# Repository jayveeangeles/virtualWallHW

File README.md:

# virtualWallHW

## Project Brief:
Repository to hold EAGLE files for Roomba Virtual Wall using PIC12F683

## Notes:
1) R7 was replaced by a 0 ohm resistor. 
2) C6 was also removed from the circuit. 
3) [SeeedStudio script](http://support.seeedstudio.com/knowledgebase/articles/1176949-how-to-generate-gerber-file-from-eagle) was used to generate manufacturing files.
4) Only the panelized brd file is included in this package. The schematic of the other board will be posted once that has been verified.

## Firmware:
[Firmware link](https://github.com/jayveeangeles/virtualWallFW)

## References:
1) [High-Speed Layout Guidelines](http://www.ti.com/lit/an/scaa082a/scaa082a.pdf)
2) [Oscillator](http://ww1.microchip.com/downloads/en/DeviceDoc/31002a.pdf)
3) [EXTERNAL 32.768 KHZ CRYSTAL OSCILLATOR](https://www.silabs.com/documents/public/application-notes/AN299.pdf)
4) [Choosing the Right Crystal and Caps for your Design](https://blog.adafruit.com/2012/01/24/choosing-the-right-crystal-and-caps-for-your-design/)
5) [Summary of Eagle PCB Layout Guidelines](https://iotexpert.com/2016/11/16/eagle-pcb-layout-guidelines-osh-park/)
6) [Using EAGLE: Board Layout](https://learn.sparkfun.com/tutorials/using-eagle-board-layout)
7) [Adding copper pour in EAGLE](https://www.lucidar.me/en/eagle/adding-copper-pour-in-eagle/)
8) [EAGLE: Panelizing made easy](https://smdprutser.nl/blog/eagle-panelizing-made-easy/)

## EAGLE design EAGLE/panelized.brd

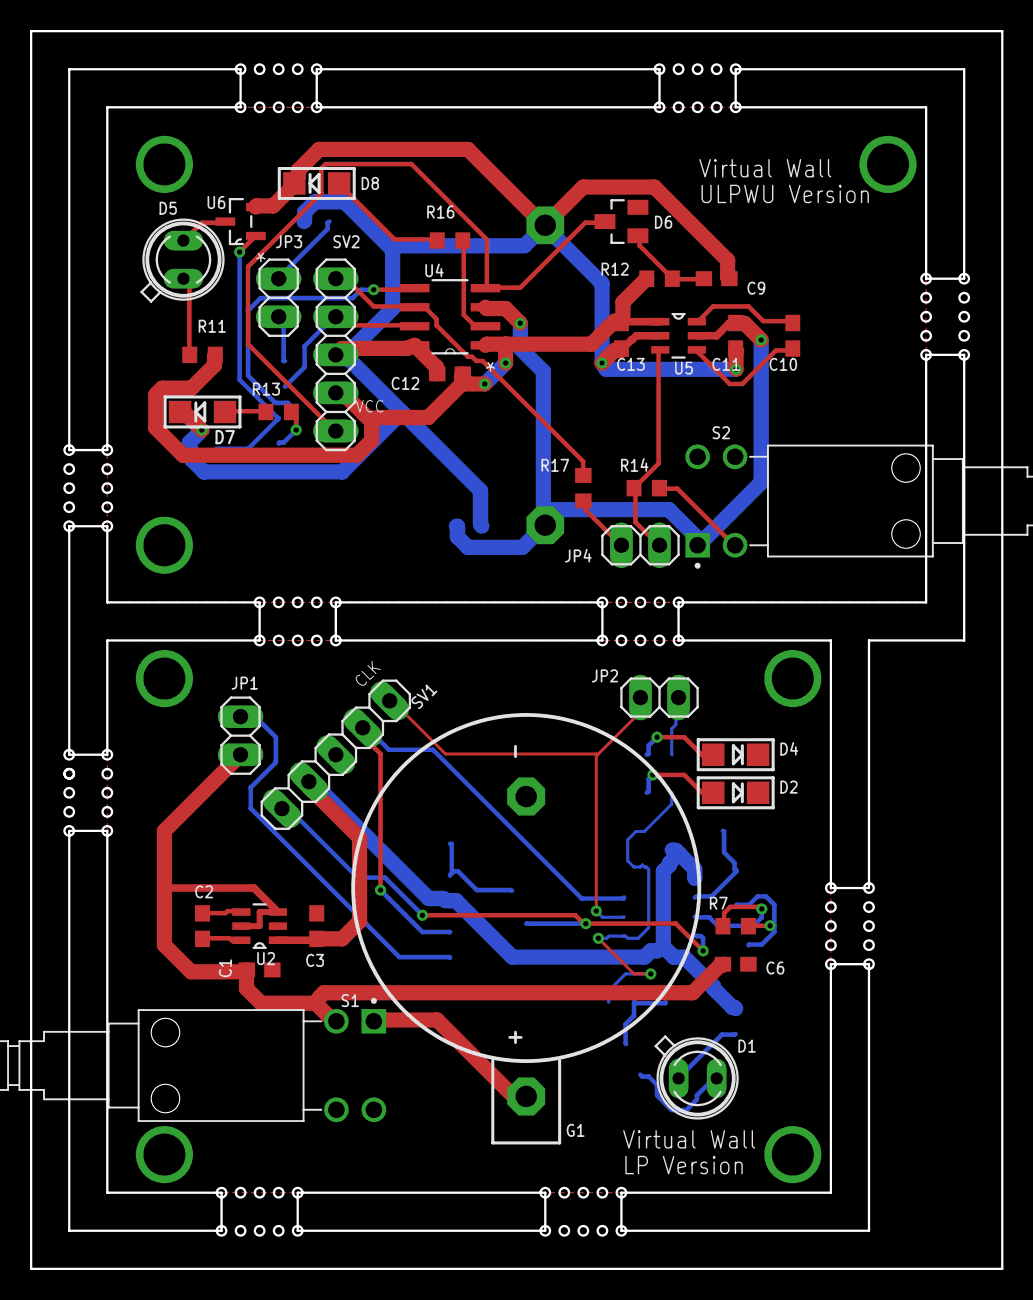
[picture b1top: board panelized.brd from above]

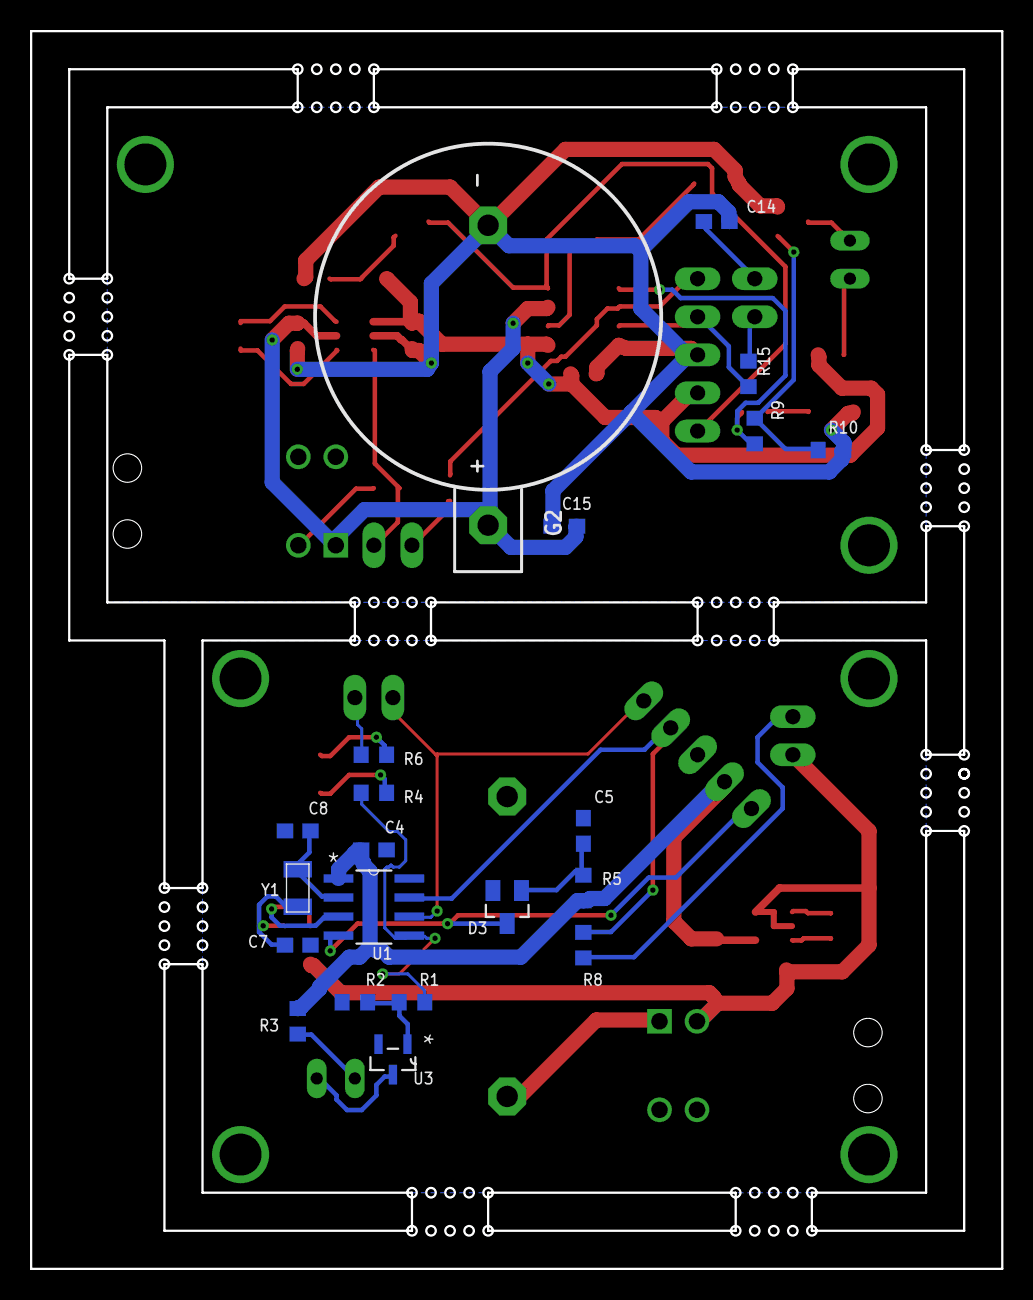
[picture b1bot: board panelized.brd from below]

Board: 2 copper layers, 64.8 x 82.6 mm, 57 parts (21 on the bottom side), 42 nets.

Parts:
C1, C2, C3, C10, C11, C13: 1u; C0603
C4, C5, C6, C9, C12, C15: 0.1u; C0603
C7, C8: 12p; C0603
C14: 50n; C0603
D1, D5: SFH482
D2, D4, D7, D8: CHIPLED_1206
D3, D6: BAT54; SOT23
G1, G2: 1066
JP1, JP2, JP3, JP4: 1X02
R1, R9: 510; R0603
R2, R5, R10, R12, R17: 10K; R0603
R3, R11: 51; R0603
R4, R6, R13, R16: 330; R0603
R7: 100; R0603
R8, R14: 1K; R0603
R15: 220; R0603
S1, S2: PB400EEQX; SW_PB400EEQX
SV1, SV2: 1X05
U1, U4: PIC12F683-I/SN; SOIC127P600X175-8N
U2, U5: CAT3200TDI-GT3; SOT95P280X100-6N
U3, U6: BSS138-7-F; SOT95P240X110-3N
Y1: CRYSTAL.ABS07; ABS07

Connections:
/SHDN: JP4.2, R14.1, U5.3
CCP1: R1.1, R4.1, U1.5
CCP2: R9.1, R13.1, U4.5
GND: C1.2, C3.2, C4.2, C5.2, C6.2, C7.1, C8.1, D2.C, D4.C, G1.-, R2.1, SV1.3, U1.8, U2.2, U3.2
GND1: C9.2, C11.2, C12.2, C13.2, C14.2, C15.2, D7.C, D8.C, G2.-, R10.1, SV2.3, U4.8, U5.2, U6.2
GP5: R16.1, U4.2
ICSPCLK: JP2.1, SV1.5, U1.6
ICSPCLK1: R17.2, SV2.5, U4.6
ICSPDAT: R8.2, SV1.4, U1.7
ICSPDAT1: R15.2, SV2.4, U4.7
MCLR: D3.3, SV1.1, U1.4
MCLR1: D6.3, SV2.1, U4.4
unnamed: C2.1, U2.4
unnamed: R1.2, R2.2, U3.1
unnamed: C2.2, U2.6
unnamed: D2.A, R4.2
unnamed: D1.A, R3.1
unnamed: D1.K, U3.3
unnamed: C5.1, D3.1, R5.1
unnamed: C7.2, R7.2, Y1.1
unnamed: D4.A, R6.2
unnamed: JP2.2, R6.1
unnamed: JP1.1, R8.1
unnamed: R9.2, R10.2, U6.1
unnamed: D5.A, R11.1
unnamed: D5.K, U6.3
unnamed: C9.1, D6.1, R12.1
unnamed: C10.2, U5.6
unnamed: C10.1, U5.4
unnamed: D7.A, R13.2
unnamed: R14.2, S2.2
unnamed: D8.A, R16.2
unnamed: C14.1, JP3.2
unnamed: JP4.1, R17.1
unnamed: JP3.1, R15.1
OSC1: C8.2, U1.2, Y1.2
OSC2: R7.1, U1.3
VBAT: G1.+, S1.1
VBAT1: C11.1, C15.1, G2.+, S2.1, U4.3, U5.5
VBAT_1: C1.1, C6.1, JP1.2, S1.2, U2.3, U2.5
VDD: C3.1, C4.1, R3.2, R5.2, SV1.2, U1.1, U2.1
VDD1: C12.1, C13.1, R11.2, R12.2, SV2.2, U4.1, U5.1

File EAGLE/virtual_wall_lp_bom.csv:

"Qty";"Value";"Device";"Package";"Parts";"Description";"AVAILABILITY";"DESCRIPTION";"MF";"MP";"MPN";"OC_FARNELL";"OC_NEWARK";"PACKAGE";"PRICE";"SPICEPREFIX";"SUPPLIER";
"2";"";"LED1206";"CHIPLED_1206";"D2, D4";"LED";"";"";"";"";"";"";"";"";"";"";"";
"2";"";"PINHD-1X2";"1X02";"JP1, JP2";"PIN HEADER";"";"";"";"";"";"";"";"";"";"";"";
"1";"";"PINHD-1X5";"1X05";"SV1";"PIN HEADER";"";"";"";"";"";"";"";"";"";"";"";
"1";"0";"R-US_R0603";"R0603";"R7";"RESISTOR, American symbol";"";"";"";"";"";"";"";"";"";"R";"";
"3";"0.1u";"C-EUC0603";"C0603";"C4, C5, C6";"CAPACITOR, European symbol";"";"";"";"";"";"";"";"";"";"";"";
"1";"1066";"1066";"1066";"G1";"Keystone 1066 Li Coin Cell Holder";"Good";" Coin Cell Holder";" 20 mm";" 0.896 in.";" Glass Filled Nylon";" Tin Plate";" 1 ";"Greenlee Communications";"1066";"";"";
"2";"10K";"R-US_R0603";"R0603";"R2, R5";"RESISTOR, American symbol";"";"";"";"";"";"";"";"";"";"R";"";
"2";"12p";"C-EUC0603";"C0603";"C7, C8";"CAPACITOR, European symbol";"";"";"";"";"";"";"";"";"";"";"";
"1";"1K";"R-US_R0603";"R0603";"R8";"RESISTOR, American symbol";"";"";"";"";"";"";"";"";"";"R";"";
"3";"1u";"C-EUC0603";"C0603";"C1, C2, C3";"CAPACITOR, European symbol";"";"";"";"";"";"";"";"";"";"";"";
"2";"330";"R-US_R0603";"R0603";"R4, R6";"RESISTOR, American symbol";"";"";"";"";"";"";"";"";"";"R";"";
"1";"51";"R-US_R0603";"R0603";"R3";"RESISTOR, American symbol";"";"";"";"";"";"";"";"";"";"R";"";
"1";"510";"R-US_R0603";"R0603";"R1";"RESISTOR, American symbol";"";"";"";"";"";"";"";"";"";"R";"";
"1";"BAT54";"BAT54";"SOT23";"D3";"Schottky barrier diodePlanar Schottky barrier diode encapsulated in small plastic SMD packages. Single diodes and double";"";"";"";"";"";"";"";"";"";"";"";
"1";"BSS138-7-F";"BSS138-7-F";"SOT95P240X110-3N";"U3";"ENHANCEMENT MODE MOSFET";"";"";"";"";"BSS138-7-F";"1843693";"12T1442";"SOT-23-3";"";"";"DIODES INC.";
"1";"CAT3200TDI-GT3";"CAT3200TDI-GT3";"SOT95P280X100-6N";"U2";"DC-DC Converter";"Good";" Regulated Charge Pump, Low Noise, DC-DC Converter ";"ON Semiconductor";"CAT3200TDI-GT3";"";"";"";"TSOT-23-6 ON Semiconductor";"0.79 USD";"";"";
"1";"CRYSTAL.ABS07";"CRYSTAL.ABS07";"ABS07";"Y1";"";"";"";"";"";"";"";"";"";"";"";"";
"1";"PB400EEQX";"PB400EEQX";"SW_PB400EEQX";"S1";"Right Angle Pushbutton Switch";"Warning";" Right Angle Pushbutton Switch ";"E-Switch";"PB400EEQX";"";"";"";"None";"0.96 USD";"";"";
"1";"PIC12F683-I/SN";"PIC12F683-I/SN";"SOIC127P600X175-8N";"U1";"IC, 8BIT MCU, PIC12, 20MHZ";"";"";"";"";"PIC12F683-I/SN";"9759042";"61K3434";"SOIC-8";"";"";"MICROCHIP";
"1";"SFH482";"SFH482";"SFH482";"D1";"IR LED";"";"";"";"";"";"";"";"";"";"";"";

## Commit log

2018-08-25 committing schematic and brd file(panelized) of the virtual wall LP version
2018-08-25 fixed README.md
2018-08-25 re-rendered BOM file and renamed filename
2018-08-25 added missing net from charge pump to ucontroller vdd

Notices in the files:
parts and their libraries:
microbuilder: This work is placed in the public domain, and may be freely used for commercial and non-commercial work with the following conditions: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
